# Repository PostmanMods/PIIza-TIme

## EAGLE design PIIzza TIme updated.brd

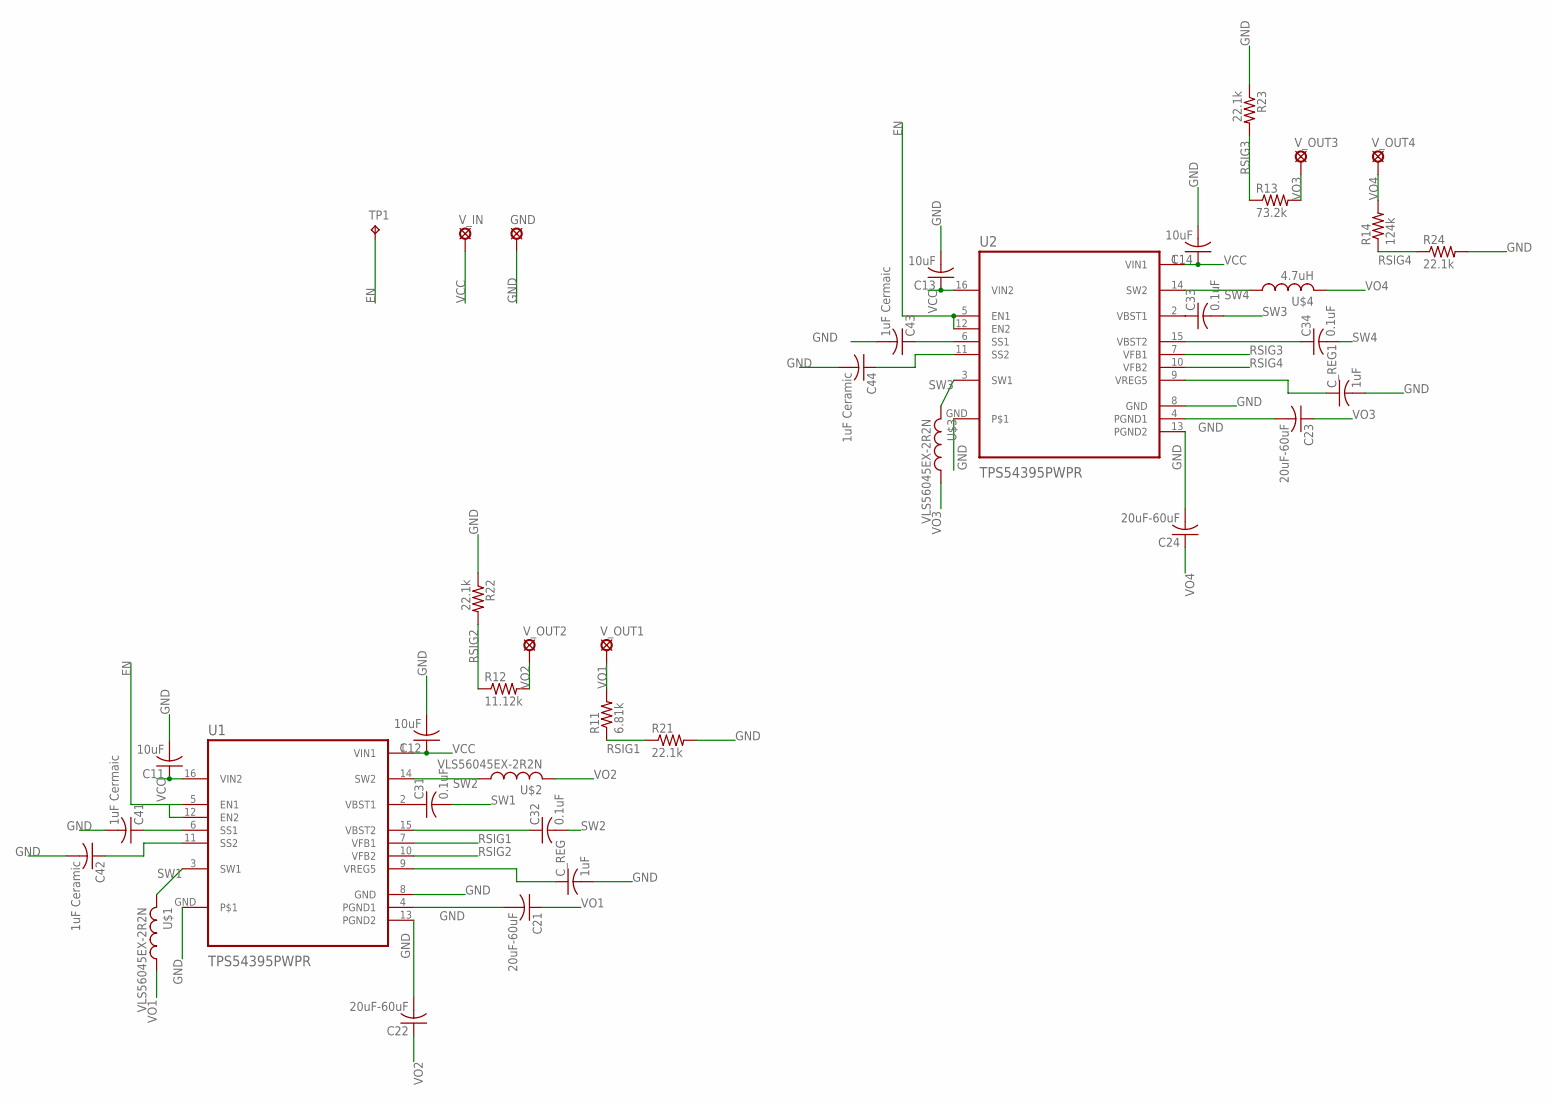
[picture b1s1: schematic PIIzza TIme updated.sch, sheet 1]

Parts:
C11, C12, C13, C14: 10uF; C0805
C21, C22, C23, C24: 20uF-60uF; C0805
C31, C32, C33, C34: 0.1uF; C0805
C41, C43: 1uF Cermaic; C0805
C42, C44: 1uF Ceramic; C0805
C_REG, C_REG1: 1uF; C0805
GND: SE11
R11: 6.81k; M0805
R12: 11.12k; M0805
R13: 73.2k; M0805
R14: 124k; M0805
R21, R22, R23, R24: 22.1k; M0805
TP1: TPB1,27; B1,27
U1, U2: TPS54395PWPR; SOP65P640X120-17N
U$1, U$2, U$3: VLS56045EX-2R2N; VLS
U$4: 4.7uH; VLS
V_IN: LSP11
V_OUT1, V_OUT2, V_OUT3, V_OUT4: LSP11

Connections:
EN: TP1.TP, U1.5 (EN1), U1.12 (EN2), U2.5 (EN1), U2.12 (EN2)
GND: C11.2, C12.2, C13.2, C14.2, C21.2, C22.2, C23.2, C24.2, C41.2, C42.2, C43.2, C44.2, C_REG.2, C_REG1.2, GND.MP, R21.2, R22.1, R23.1, R24.2, U1.4 (PGND1), U1.8 (GND), U1.13 (PGND2), U1.GND, U2.4 (PGND1), U2.8 (GND), U2.13 (PGND2), U2.GND; also elsewhere on the board
unnamed: C41.1, U1.6 (SS1)
unnamed: C42.1, U1.11 (SS2)
unnamed: C31.1, U1.2 (VBST1)
unnamed: C32.1, U1.15 (VBST2)
unnamed: C_REG.1, U1.9 (VREG5)
unnamed: C43.1, U2.6 (SS1)
unnamed: C44.1, U2.11 (SS2)
unnamed: C33.1, U2.2 (VBST1)
unnamed: C34.1, U2.15 (VBST2)
unnamed: C_REG1.1, U2.9 (VREG5)
RSIG1: R11.1, R21.1, U1.7 (VFB1)
RSIG2: R12.1, R22.2, U1.10 (VFB2)
RSIG3: R13.1, R23.2, U2.7 (VFB1)
RSIG4: R14.1, R24.1, U2.10 (VFB2)
SW1: C31.2, U1.3 (SW1), U$1.P$2 (2)
SW2: C32.2, U1.14 (SW2), U$2.P$1 (1)
SW3: C33.2, U2.3 (SW1), U$3.P$2 (2)
SW4: C34.2, U2.14 (SW2), U$4.P$1 (1)
VCC: C11.1, C12.1, C13.1, C14.1, U1.1 (VIN1), U1.16 (VIN2), U2.1 (VIN1), U2.16 (VIN2), V_IN.MP
VO1: C21.1, R11.2, U$1.P$1 (1), V_OUT1.MP
VO2: C22.1, R12.2, U$2.P$2 (2), V_OUT2.MP
VO3: C23.1, R13.2, U$3.P$1 (1), V_OUT3.MP; also elsewhere on the board
VO4: C24.1, R14.2, U$4.P$2 (2), V_OUT4.MP

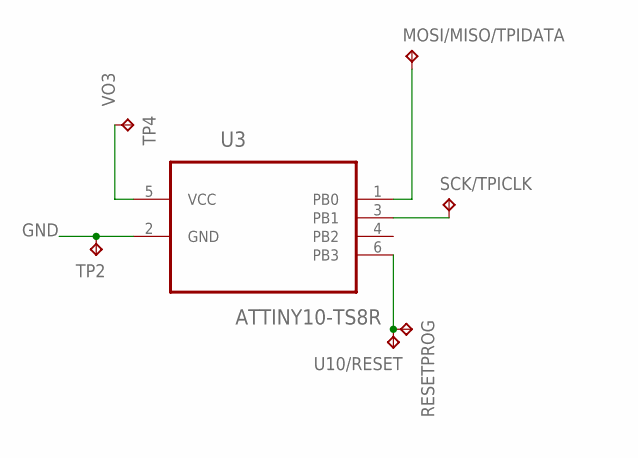
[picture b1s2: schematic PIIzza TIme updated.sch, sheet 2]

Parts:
MOSI/MISO/TPIDATA: TPB2,54; B2,54
RESETPROG: TPB2,54; B2,54
SCK/TPICLK: TPB2,54; B2,54
TP2, TP4: TPB2,54; B2,54
U3: ATTINY10-TS8R; SOT95P280X145-6N
U10/RESET: TPB2,54; B2,54

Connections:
DIS_BAT_LIFE: RESETPROG.TP, U3.6 (PB3), U10/RESET.TP
GND: TP2.TP, U3.2 (GND); also elsewhere on the board
unnamed: MOSI/MISO/TPIDATA.TP, U3.1 (PB0)
unnamed: SCK/TPICLK.TP, U3.3 (PB1)
VO3: TP4.TP, U3.5 (VCC); also elsewhere on the board

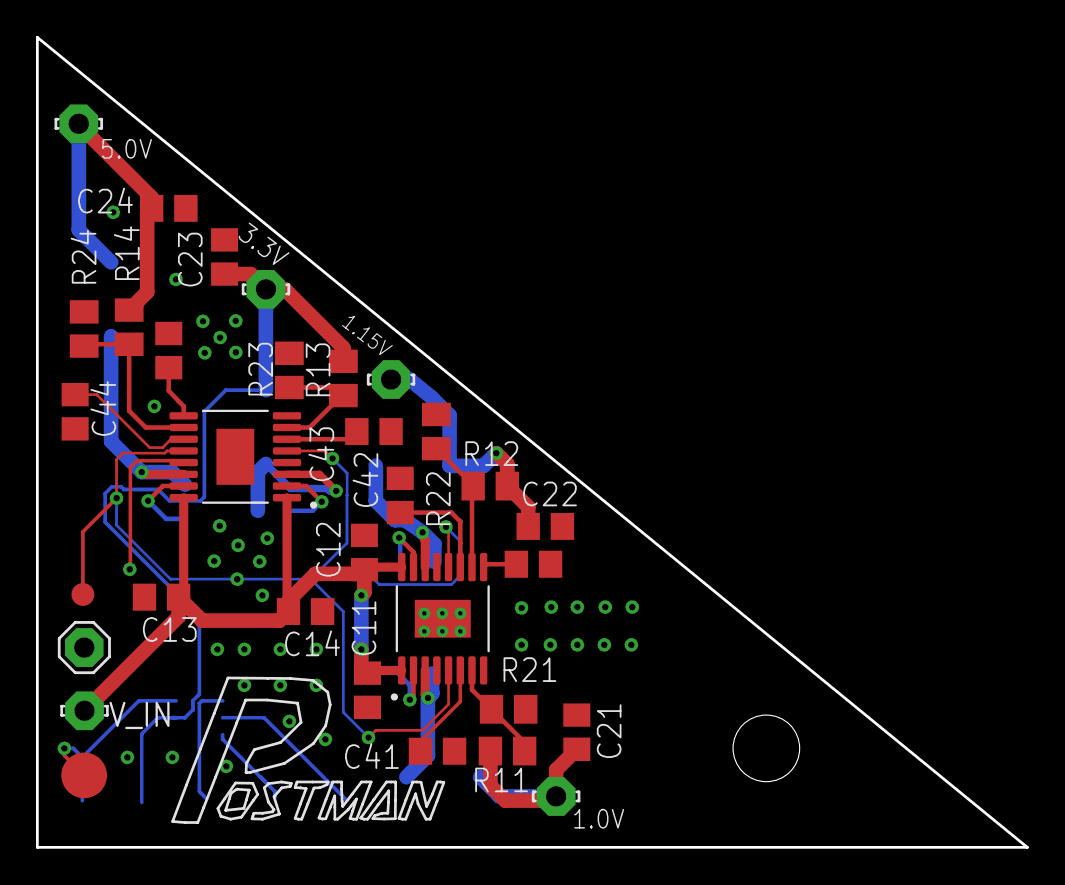
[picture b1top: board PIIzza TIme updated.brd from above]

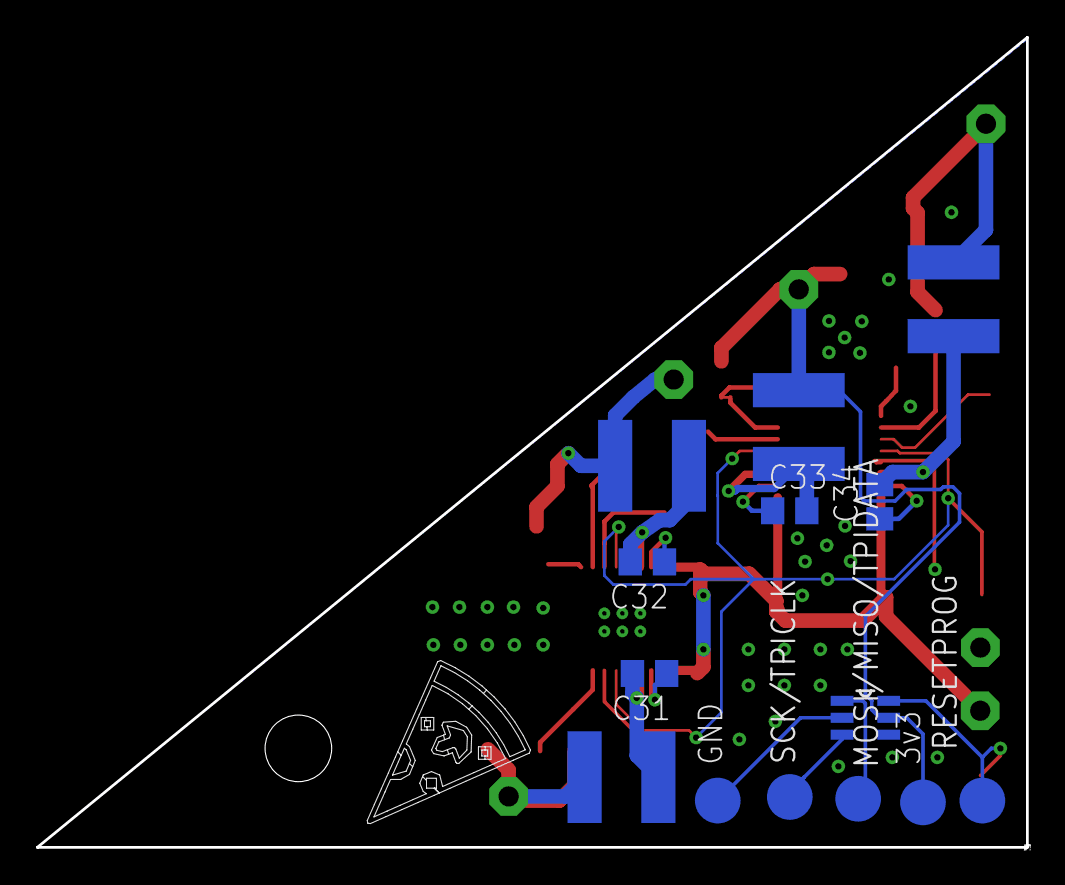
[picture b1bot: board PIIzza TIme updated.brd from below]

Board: 2 copper layers, 55.0 x 45.0 mm, 48 parts (15 on the bottom side), 28 nets.

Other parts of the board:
U$5: LOGO
U$6: PIIZATIME

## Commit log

2019-03-21 Add files via upload
    This version improves regulator cooling via exposed gnd plane with vias near the thermal pads of the regulator. It also includes an attiny10 and programming pads for the U10 point on the wii motherbo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
